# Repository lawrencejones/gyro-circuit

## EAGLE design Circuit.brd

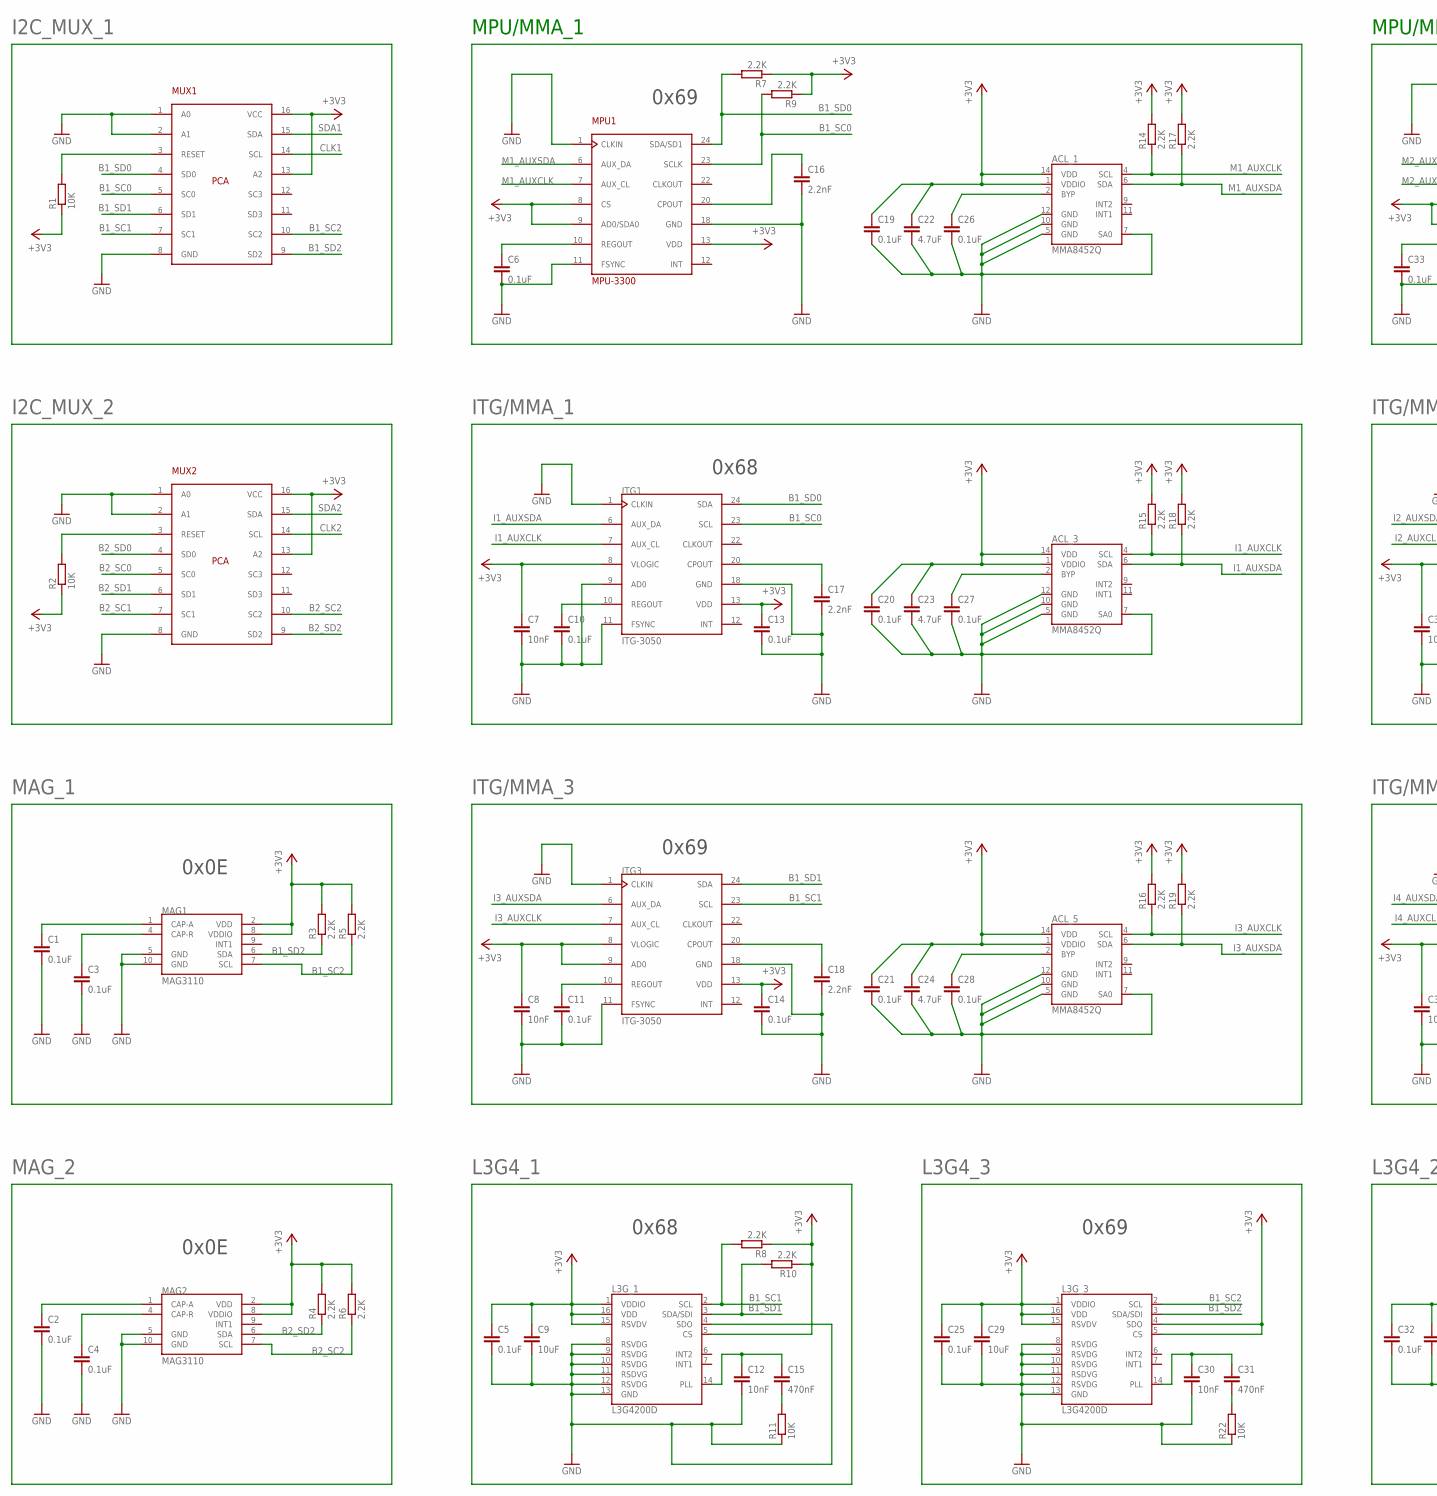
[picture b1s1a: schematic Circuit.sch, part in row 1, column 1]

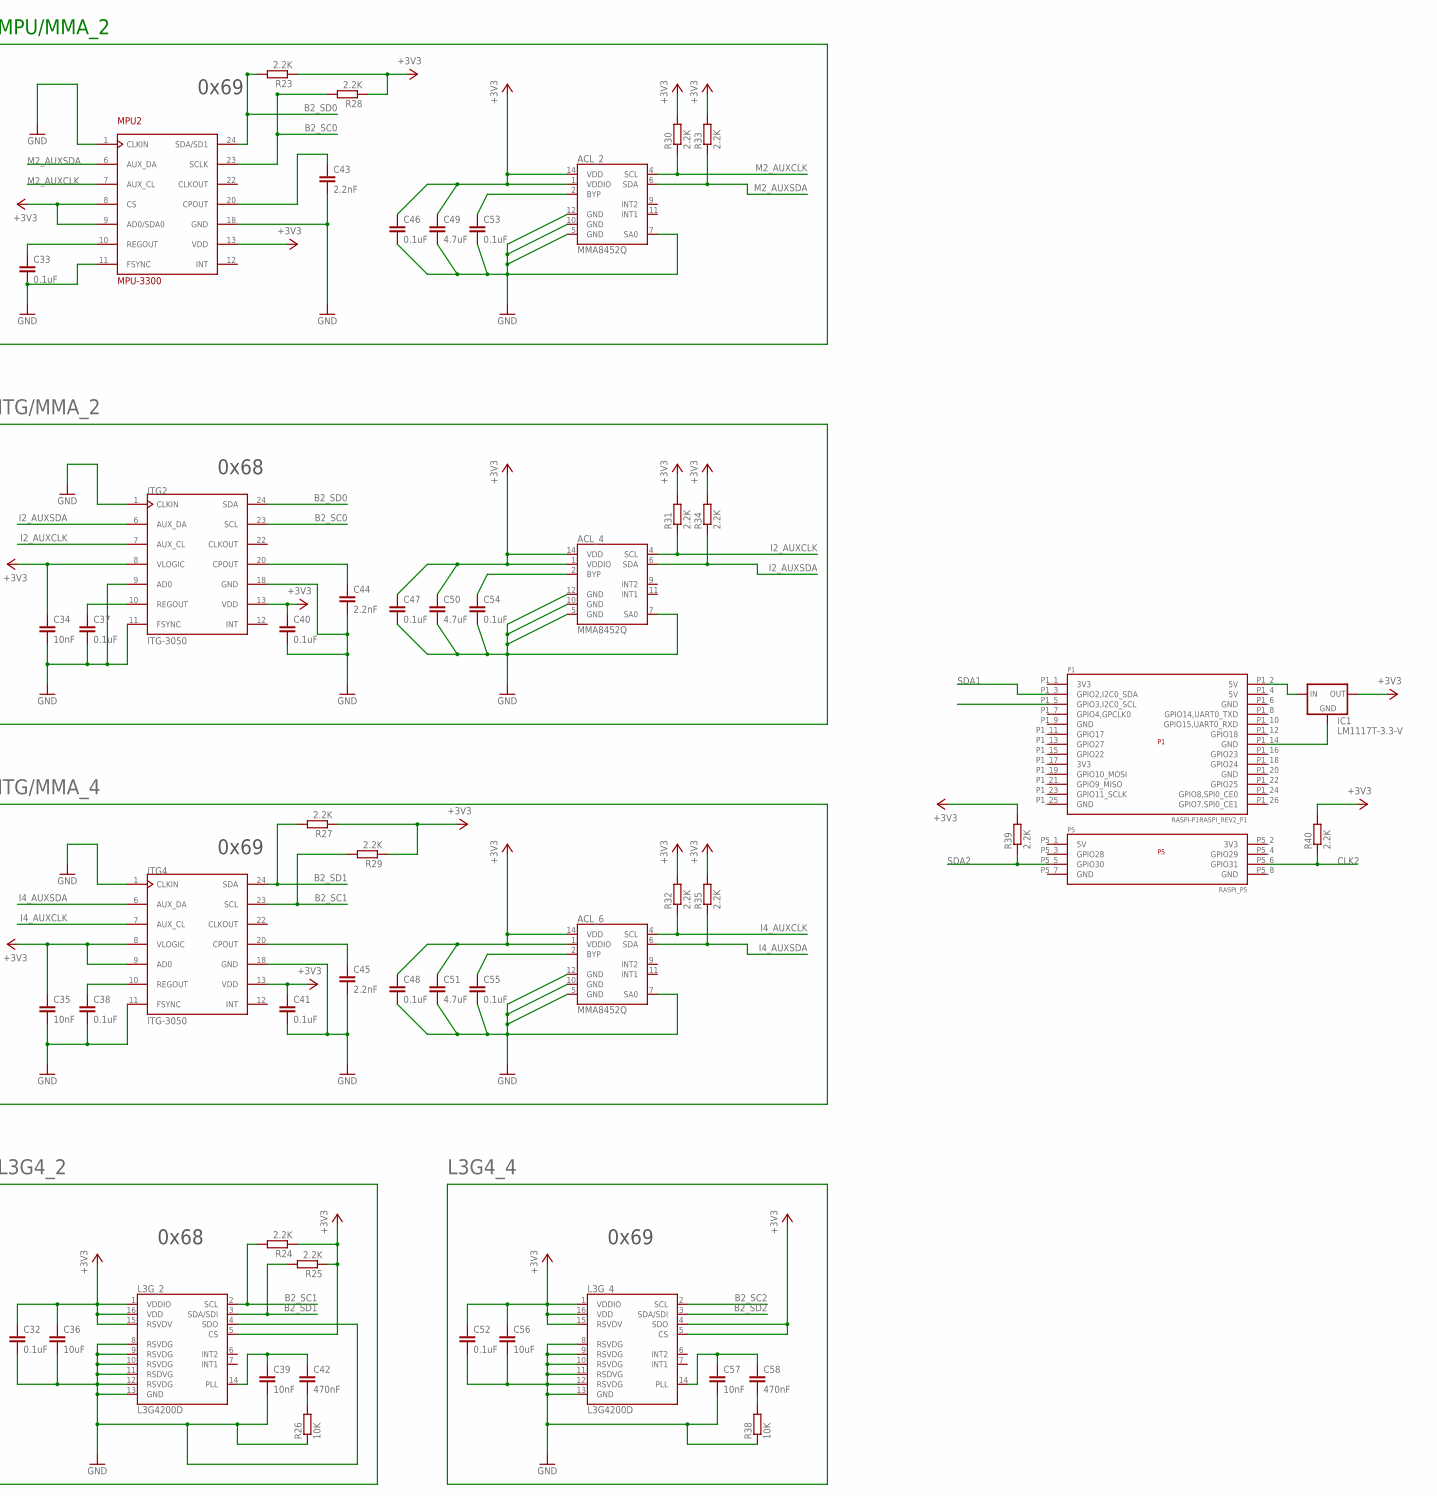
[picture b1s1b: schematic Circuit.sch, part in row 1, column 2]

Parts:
ACL_1, ACL_2, ACL_3, ACL_4, ACL_5, ACL_6: MMA8452Q; QFN-16_0.5MM
C1, C2, C3, C4, C5, C6, C10, C11, C13, C14, C19, C20, C21, C25, C26, C27, C28, C32, C33, C37, C38, C40, C41, C46, C47, C48, C52, C53, C54, C55: 0.1uF; 0603-CAP
C7, C8, C12, C30, C34, C35, C39, C57: 10nF; 0603-CAP
C9, C29, C36, C56: 10uF; 0603-CAP
C15, C31, C42, C58: 470nF; 0603-CAP
C16, C17, C18, C43, C44, C45: 2.2nF; 0603-CAP
C22, C23, C24, C49, C50, C51: 4.7uF; 0603-CAP
IC1: LM1117T-3.3-V; TO220V
ITG1, ITG2, ITG3, ITG4: ITG-3050; QFN-24-4MM2
L3G_1, L3G_2, L3G_3, L3G_4: L3G4200D; LGA16-4X4
MAG1, MAG2: MAG3110; DFN-10
MPU1, MPU2: MPU-3300; QFN-24-4MM2
MUX1, MUX2: PCA9546A; TSSOP16
P1: RASPI-P1RASPI_REV2_P1; RASPBERRY-PI_REV2
P5: RASPI_P5
R1, R2, R11, R22, R26, R38: 10K; R0603
R3, R4, R5, R6, R7, R8, R9, R10, R14, R15, R16, R17, R18, R19, R23, R24, R25, R27, R28, R29, R30, R31, R32, R33, R34, R35, R39, R40: 2.2K; R0603

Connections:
+3V3: ACL_1.1 (VDDIO), ACL_1.14 (VDD), ACL_2.1 (VDDIO), ACL_2.14 (VDD), ACL_3.1 (VDDIO), ACL_3.14 (VDD), ACL_4.1 (VDDIO), ACL_4.14 (VDD), ACL_5.1 (VDDIO), ACL_5.14 (VDD), ACL_6.1 (VDDIO), ACL_6.14 (VDD), C5.1, C7.1, C8.1, C9.1, C13.1, C14.1, C19.1, C20.1, C21.1, C22.1, C23.1, C24.1, C25.1, C29.1, C32.1, C34.1, C35.1, C36.1, C40.1, C41.1, C46.1, C47.1, C48.1, C49.1, C50.1, C51.1, C52.1, C56.1, IC1.2 (OUT), ITG1.8 (VLOGIC), ITG1.13 (VDD), ITG2.8 (VLOGIC), ITG2.13 (VDD), ITG3.8 (VLOGIC), ITG3.9 (AD0), ITG3.13 (VDD), ITG4.8 (VLOGIC), ITG4.9 (AD0), ITG4.13 (VDD), L3G_1.1 (VDDIO), L3G_1.5 (CS), L3G_1.15 (RSVDV), L3G_1.16 (VDD), L3G_2.1 (VDDIO), L3G_2.5 (CS), L3G_2.15 (RSVDV), L3G_2.16 (VDD), L3G_3.1 (VDDIO), L3G_3.4 (SDO), L3G_3.5 (CS), L3G_3.15 (RSVDV), L3G_3.16 (VDD), L3G_4.1 (VDDIO), L3G_4.4 (SDO), L3G_4.5 (CS), L3G_4.15 (RSVDV), L3G_4.16 (VDD), MAG1.2 (VDD), MAG1.8 (VDDIO), MAG2.2 (VDD), MAG2.8 (VDDIO), MPU1.8 (CS), MPU1.9 (AD0/SDA0), MPU1.13 (VDD), MPU2.8 (CS), MPU2.9 (AD0/SDA0), MPU2.13 (VDD), MUX1.13 (A2), MUX1.16 (VCC), MUX2.13 (A2), MUX2.16 (VCC), R1.1, R2.1, R3.2, R4.2, R5.2, R6.2, R7.1, R8.1, R9.1, R10.1, R14.2, R15.2, R16.2, R17.2, R18.2, R19.2, R23.1, R24.1, R25.1, R27.1, R28.1, R29.1, R30.2, R31.2, R32.2, R33.2, R34.2, R35.2, R39.2, R40.2
B1_SC0: ITG1.23 (SCL), MPU1.23 (SCLK), MUX1.5 (SC0), R9.2
B1_SC1: ITG3.23 (SCL), L3G_1.2 (SCL), MUX1.7 (SC1), R8.2
B1_SC2: L3G_3.2 (SCL), MAG1.7 (SCL), MUX1.10 (SC2), R5.1
B1_SD0: ITG1.24 (SDA), MPU1.24 (SDA/SD1), MUX1.4 (SD0), R7.2
B1_SD1: ITG3.24 (SDA), L3G_1.3 (SDA/SDI), MUX1.6 (SD1), R10.2
B1_SD2: L3G_3.3 (SDA/SDI), MAG1.6 (SDA), MUX1.9 (SD2), R3.1
B2_SC0: ITG2.23 (SCL), MPU2.23 (SCLK), MUX2.5 (SC0), R28.2
B2_SC1: ITG4.23 (SCL), L3G_2.2 (SCL), MUX2.7 (SC1), R24.2, R29.2
B2_SC2: L3G_4.2 (SCL), MAG2.7 (SCL), MUX2.10 (SC2), R6.1
B2_SD0: ITG2.24 (SDA), MPU2.24 (SDA/SD1), MUX2.4 (SD0), R23.2
B2_SD1: ITG4.24 (SDA), L3G_2.3 (SDA/SDI), MUX2.6 (SD1), R25.2, R27.2
B2_SD2: L3G_4.3 (SDA/SDI), MAG2.6 (SDA), MUX2.9 (SD2), R4.1
CLK1: MUX1.14 (SCL), P1.P1_5 (GPIO3,I2C0_SCL)
CLK2: MUX2.14 (SCL), P5.P5_6 (GPIO31), R40.1
GND: ACL_1.5 (GND), ACL_1.7 (SA0), ACL_1.10 (GND), ACL_1.12 (GND), ACL_2.5 (GND), ACL_2.7 (SA0), ACL_2.10 (GND), ACL_2.12 (GND), ACL_3.5 (GND), ACL_3.7 (SA0), ACL_3.10 (GND), ACL_3.12 (GND), ACL_4.5 (GND), ACL_4.7 (SA0), ACL_4.10 (GND), ACL_4.12 (GND), ACL_5.5 (GND), ACL_5.7 (SA0), ACL_5.10 (GND), ACL_5.12 (GND), ACL_6.5 (GND), ACL_6.7 (SA0), ACL_6.10 (GND), ACL_6.12 (GND), C1.2, C2.2, C3.2, C4.2, C5.2, C6.2, C7.2, C8.2, C9.2, C10.2, C11.2, C12.2, C13.2, C14.2, C16.2, C17.2, C18.2, C19.2, C20.2, C21.2, C22.2, C23.2, C24.2, C25.2, C26.2, C27.2, C28.2, C29.2, C30.2, C32.2, C33.2, C34.2, C35.2, C36.2, C37.2, C38.2, C39.2, C40.2, C41.2, C43.2, C44.2, C45.2, C46.2, C47.2, C48.2, C49.2, C50.2, C51.2, C52.2, C53.2, C54.2, C55.2, C56.2, C57.2, IC1.1 (GND), ITG1.1 (CLKIN), ITG1.9 (AD0), ITG1.11 (FSYNC), ITG1.18 (GND), ITG2.1 (CLKIN), ITG2.9 (AD0), ITG2.11 (FSYNC), ITG2.18 (GND), ITG3.1 (CLKIN), ITG3.11 (FSYNC), ITG3.18 (GND), ITG4.1 (CLKIN), ITG4.11 (FSYNC), ITG4.18 (GND), L3G_1.4 (SDO), L3G_1.8 (RSVDG), L3G_1.9 (RSVDG), L3G_1.10 (RSVDG), L3G_1.11 (RSDVG), L3G_1.12 (RSVDG), L3G_1.13 (GND), L3G_2.4 (SDO), L3G_2.8 (RSVDG), L3G_2.9 (RSVDG), L3G_2.10 (RSVDG), L3G_2.11 (RSDVG), L3G_2.12 (RSVDG), L3G_2.13 (GND), L3G_3.8 (RSVDG), L3G_3.9 (RSVDG), L3G_3.10 (RSVDG), L3G_3.11 (RSDVG), L3G_3.12 (RSVDG), L3G_3.13 (GND), L3G_4.8 (RSVDG), L3G_4.9 (RSVDG), L3G_4.10 (RSVDG), L3G_4.11 (RSDVG), L3G_4.12 (RSVDG), L3G_4.13 (GND), MAG1.5 (GND), MAG1.10 (GND), MAG2.5 (GND), MAG2.10 (GND), MPU1.1 (CLKIN), MPU1.11 (FSYNC), MPU1.18 (GND), MPU2.1 (CLKIN), MPU2.11 (FSYNC), MPU2.18 (GND), MUX1.1 (A0), MUX1.2 (A1), MUX1.8 (GND), MUX2.1 (A0), MUX2.2 (A1), MUX2.8 (GND), P1.P1_14 (GND), R11.1, R22.1, R26.1, R38.1
I1_AUXCLK: ACL_3.4 (SCL), ITG1.7 (AUX_CL), R15.1
I1_AUXSDA: ACL_3.6 (SDA), ITG1.6 (AUX_DA), R18.1
I2_AUXCLK: ACL_4.4 (SCL), ITG2.7 (AUX_CL), R31.1
I2_AUXSDA: ACL_4.6 (SDA), ITG2.6 (AUX_DA), R34.1
I3_AUXCLK: ACL_5.4 (SCL), ITG3.7 (AUX_CL), R16.1
I3_AUXSDA: ACL_5.6 (SDA), ITG3.6 (AUX_DA), R19.1
I4_AUXCLK: ACL_6.4 (SCL), ITG4.7 (AUX_CL), R32.1
I4_AUXSDA: ACL_6.6 (SDA), ITG4.6 (AUX_DA), R35.1
M1_AUXCLK: ACL_1.4 (SCL), MPU1.7 (AUX_CL), R14.1
M1_AUXSDA: ACL_1.6 (SDA), MPU1.6 (AUX_DA), R17.1
M2_AUXCLK: ACL_2.4 (SCL), MPU2.7 (AUX_CL), R30.1
M2_AUXSDA: ACL_2.6 (SDA), MPU2.6 (AUX_DA), R33.1
unnamed: C16.1, MPU1.20 (CPOUT)
unnamed: C6.1, MPU1.10 (REGOUT)
unnamed: ACL_1.2 (BYP), C26.1
unnamed: ACL_2.2 (BYP), C53.1
unnamed: C43.1, MPU2.20 (CPOUT)
unnamed: C33.1, MPU2.10 (REGOUT)
unnamed: ACL_3.2 (BYP), C27.1
unnamed: IC1.3 (IN), P1.P1_2 (5V)
unnamed: C10.1, ITG1.10 (REGOUT)
unnamed: C17.1, ITG1.20 (CPOUT)
unnamed: ACL_4.2 (BYP), C54.1
unnamed: MUX2.3 (RESET), R2.2
unnamed: C37.1, ITG2.10 (REGOUT)
unnamed: C44.1, ITG2.20 (CPOUT)
unnamed: ACL_5.2 (BYP), C28.1
unnamed: C11.1, ITG3.10 (REGOUT)
unnamed: C18.1, ITG3.20 (CPOUT)
unnamed: ACL_6.2 (BYP), C55.1
unnamed: C38.1, ITG4.10 (REGOUT)
unnamed: C45.1, ITG4.20 (CPOUT)
unnamed: C30.1, C31.1, L3G_3.14 (PLL)
unnamed: C2.1, MAG2.1 (CAP-A)
unnamed: C12.1, C15.1, L3G_1.14 (PLL)
unnamed: C15.2, R11.2
unnamed: C31.2, R22.2
unnamed: MUX1.3 (RESET), R1.2
unnamed: C39.1, C42.1, L3G_2.14 (PLL)
unnamed: C42.2, R26.2
unnamed: C4.1, MAG2.4 (CAP-R)
unnamed: C57.1, C58.1, L3G_4.14 (PLL)
unnamed: C58.2, R38.2
unnamed: C1.1, MAG1.1 (CAP-A)
unnamed: C3.1, MAG1.4 (CAP-R)
SDA1: MUX1.15 (SDA), P1.P1_3 (GPIO2,I2C0_SDA)
SDA2: MUX2.15 (SDA), P5.P5_5 (GPIO30), R39.1

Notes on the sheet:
MPU/MMA_1
MPU/MMA_2
0x69
0x68
0x0E

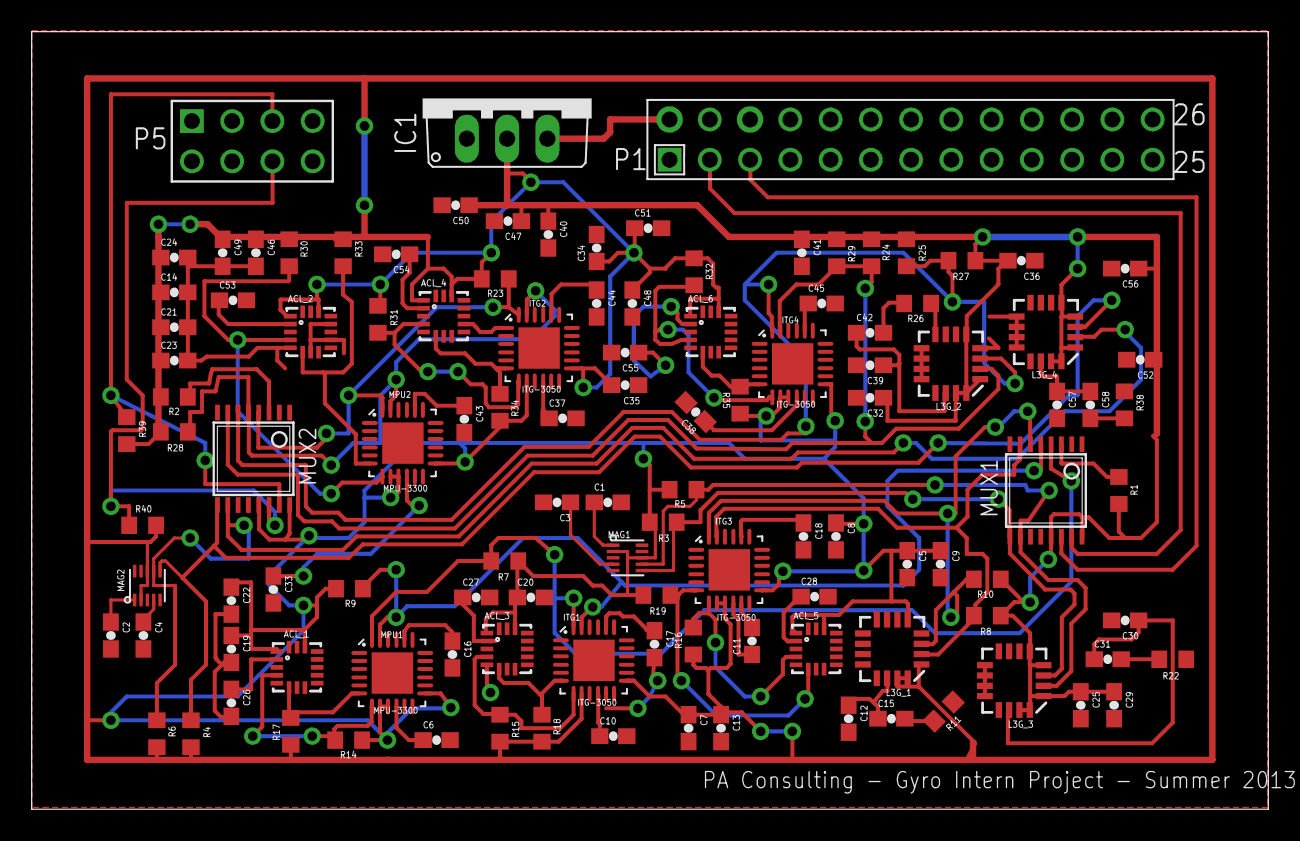
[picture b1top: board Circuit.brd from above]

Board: 2 copper layers, 78.0 x 49.1 mm, 115 parts (0 on the bottom side), 63 nets.

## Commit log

2013-07-25 Initial commit of gyro lib and circuit
2013-07-25 Added all the sensor components
2013-07-25 Adds first routes
2013-07-26 Added 4 itg setups
2013-07-26 Added L3G4 gyros
2013-07-26 Added mags and box labels
2013-07-31 Organised the board layout, requires autorouting
2013-07-31 Rearranged as per phil
2013-08-01 Changes to raspi headers
2013-08-01 Corrected erc violations
2013-08-01 Finalises packages, adds labels to homemade stuff
2013-08-01 Placed test pads
2013-08-01 Initial board layout complete
2013-08-01 Poured copper top + bottom, GND
2013-08-01 Moved resistor labels
2013-08-02 Temporarily removed polygons
2013-08-02 Corrected GND connection
2013-08-02 Removed the test pads
2013-08-02 Spaced board out
2013-08-02 Started hand routeing
2013-08-04 First side 80% of 90%. Not that far in total :/
2013-08-05 Stashing prior to optimisation of resistors
2013-08-05 Removed pointless resistors
2013-08-05 Halfway
2013-08-05 <paranoia>COMMIT!</paranoia>
2013-08-05 About to find a load of problems. Ignorance is bliss.
2013-08-05 Magnometer left
2013-08-05 Fixing a few schematic errors
2013-08-05 Finished preliminary component positioning + routeing
2013-08-05 Changed to smashed raspi headers
2013-08-05 Prior to removal of interupt wires
2013-08-05 Rearranging buses
2013-08-05 Addressing DRC issues
2013-08-05 All simple design rule checks performed
2013-08-05 Stash
2013-08-05 Added via
2013-08-05 Going home
2013-08-05 Leaving
2013-08-05 Sorting out missing connections
2013-08-05 Slowly does it
2013-08-05 Pause before Skins. I think I've got all airwires?
2013-08-05 Before pouring copper
2013-08-05 Adding wires for grounds
2013-08-06 Going home now!
2013-08-07 Stashing for safety
2013-08-07 Going home again!
2013-08-08 On train
2013-08-08 4 Airwaves left
2013-08-08 No more wires!
2013-08-08 All none mag related drc errors resolved
2013-08-08 Switched to 0.2mm wires for mag connections
2013-08-08 Changed label sizes
2013-08-09 Adds cam files and specs
2013-09-07 Corrects pin connect for the raspi header
2013-09-24 Modified labels
2013-10-25 Packaging for handover
